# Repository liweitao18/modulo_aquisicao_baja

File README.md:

# modulo_aquisicao_baja
Projeto de modulo de aquisição de dados de um veículo baja SAE

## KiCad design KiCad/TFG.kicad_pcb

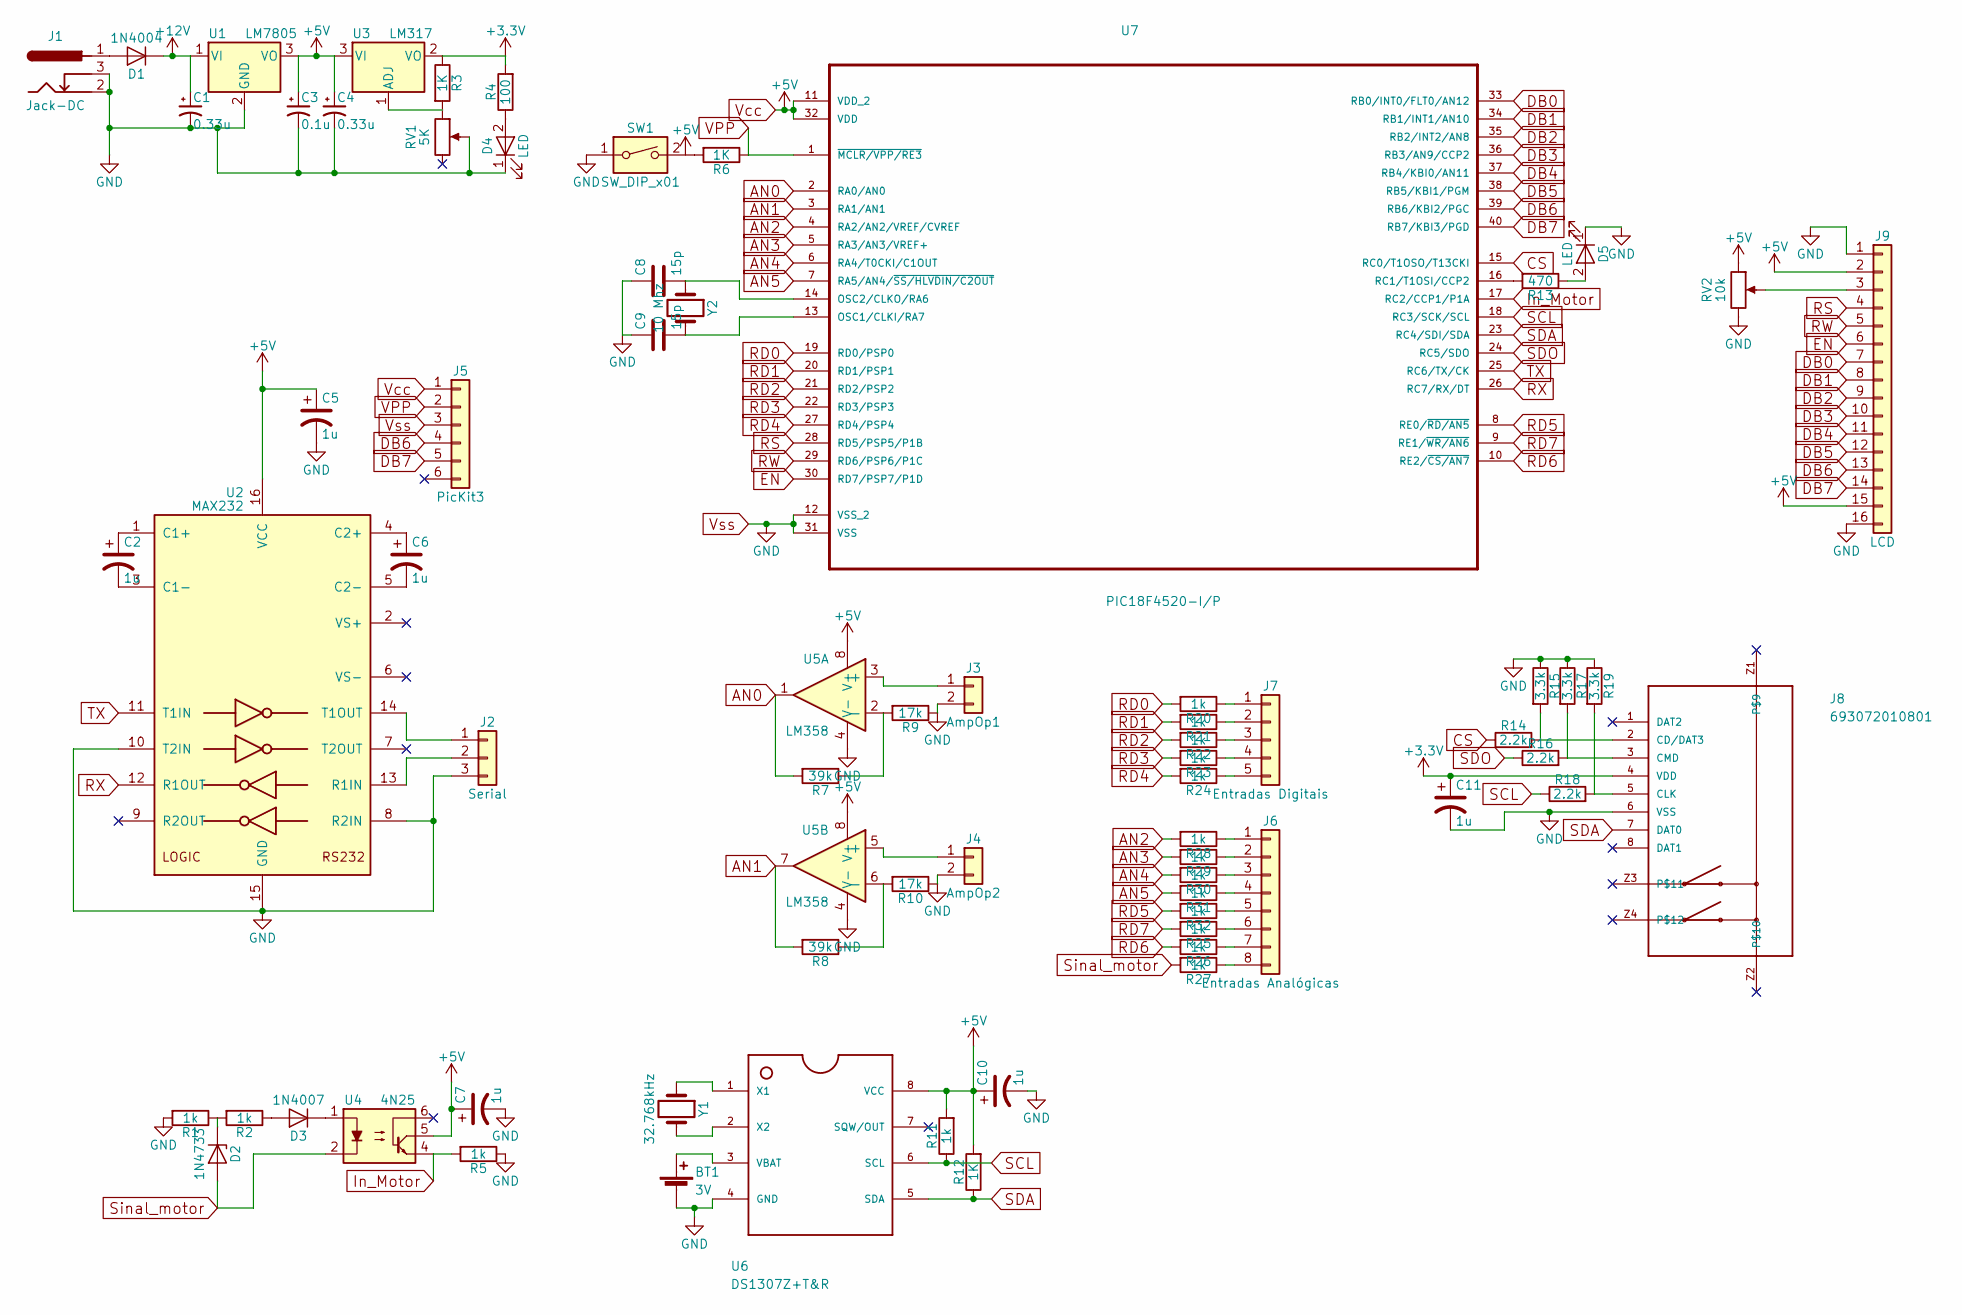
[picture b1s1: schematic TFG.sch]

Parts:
BT1: 3V; Keystone_104_1x23mm-CoinCell
C1, C4: 0.33u; CP_Tantalum_Case-A_EIA-3216-18_Hand
C2, C5, C6, C7, C10, C11: 1u; CP_Tantalum_Case-A_EIA-3216-18_Hand
C3: 0.1u; CP_Tantalum_Case-A_EIA-3216-18_Hand
C8, C9: 15p; C_0201
D1: 1N4004; D_0603
D2: 1N4733; D_0603
D3: 1N4007; D_0603
D4, D5: LED; LED_0402
J1: Jack-DC; GCT_DCJ235-05-A-XX-X_REVA
J2: Serial; Pin_Header_Straight_1x03_Pitch2.00mm
J3: AmpOp1; Pin_Header_Straight_1x02_Pitch2.54mm
J4: AmpOp2; Pin_Header_Straight_1x02_Pitch2.54mm
J5: PicKit3; Pin_Header_Straight_1x06_Pitch2.00mm
J6: Entradas Analógicas; Pin_Header_Straight_1x08_Pitch2.00mm
J7: Entradas Digitais; Pin_Header_Straight_1x05_Pitch2.00mm
J8: 693072010801
J9: LCD; Socket_Strip_Straight_1x16_Pitch2.00mm
R1, R2, R5, R11, R20, R21, R22, R23, R24, R25, R26, R27, R28, R29, R30, R31, R32: 1k; R_0805_HandSoldering
R3, R6, R12: 1K; R_0805_HandSoldering
R4: 100; R_0805_HandSoldering
R7, R8: 39k; R_0805_HandSoldering
R9, R10: 17k; R_0805_HandSoldering
R13: 470; R_0805_HandSoldering
R14, R16, R18: 2.2k; R_0805_HandSoldering
R15, R17, R19: 3.3k; R_0805_HandSoldering
RV1: 5K; Potentiometer_Trimmer_Bourns_3266Y
RV2: 10k; Potentiometer_Trimmer_Bourns_3266Y
SW1: SW_DIP_x01; SW_DIP_x1_W5.08mm_Slide_Copal_CHS-A
U1: LM7805; TO-220-3_Vertical
U2: MAX232; DIP-16_W7.62mm_Socket
U3: LM317; TO-220-3_Vertical
U4: 4N25; DIP-6_W7.62mm_Socket
U5: LM358; DIP-8_W7.62mm_Socket
U6: DS1307Z+T&R; DIP-8_W7.62mm_Socket
U7: PIC18F4520-I/P; DIP254P1524X533-40
Y1: 32.768kHz; Crystal_AT310_d3.0mm_l10.0mm_Vertical
Y2: 10 Mhz; Crystal_HC18-U_Vertical

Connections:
+3V3: C11.1, J8.4 (VDD), R3.1, R4.2, U3.2 (VO)
+12V: C1.1, D1.1 (K), U1.1 (VI)
AN0: R7.2, U5.1, U7.2 (RA0/AN0)
AN1: R8.2, U5.7, U7.3 (RA1/AN1)
AN2: R28.2, U7.4 (RA2/AN2/VREF/CVREF)
AN3: R29.2, U7.5 (RA3/AN3/VREF+)
AN4: R30.2, U7.6 (RA4/T0CKI/C1OUT)
AN5: R31.2, U7.7 (RA5/AN4/~SS/HLVDIN/C2OUT)
CS: R14.1, U7.15 (RC0/T1OSO/T13CKI)
DB0: J9.7, U7.33 (RB0/INT0/FLT0/AN12)
DB1: J9.8, U7.34 (RB1/INT1/AN10)
DB2: J9.9, U7.35 (RB2/INT2/AN8)
DB3: J9.10, U7.36 (RB3/AN9/CCP2)
DB4: J9.11, U7.37 (RB4/KBI0/AN11)
DB5: J9.12, U7.38 (RB5/KBI1/PGM)
DB6: J5.4, J9.13, U7.39 (RB6/KBI2/PGC)
DB7: J5.5, J9.14, U7.40 (RB7/KBI3/PGD)
EN: J9.6, U7.30 (RD7/PSP7/P1D)
In_Motor: R5.2, U4.4, U7.17 (RC2/CCP1/P1A)
unnamed: BT1.1 (+), U6.3 (VBAT)
unnamed: C2.1, U2.1 (C1+)
unnamed: C2.2, U2.3 (C1-)
unnamed: C6.1, U2.4 (C2+)
unnamed: C6.2, U2.5 (C2-)
unnamed: C8.2, U7.14 (OSC2/CLKO/RA6), Y2.1
unnamed: C9.2, U7.13 (OSC1/CLKI/RA7), Y2.2
unnamed: D1.2 (A), J1.1
unnamed: D2.1 (K), R1.1, R2.2
unnamed: D3.1 (K), U4.1
unnamed: D3.2 (A), R2.1
unnamed: D4.2 (A), R4.1
unnamed: D5.2 (A), R13.1
unnamed: J2.1, U2.14 (T1OUT)
unnamed: J2.2, U2.13 (R1IN)
unnamed: J3.1, U5.3 (+)
unnamed: J4.1, U5.5 (+)
unnamed: J6.1, R28.1
unnamed: J6.2, R29.1
unnamed: J6.3, R30.1
unnamed: J6.4, R31.1
unnamed: J6.5, R32.1
unnamed: J6.6, R25.1
unnamed: J6.7, R26.1
unnamed: J6.8, R27.1
unnamed: J7.1, R20.1
unnamed: J7.2, R21.1
unnamed: J7.3, R22.1
unnamed: J7.4, R23.1
unnamed: J7.5, R24.1
unnamed: J8.2 (CD/DAT3), R14.2, R15.2
unnamed: J8.3 (CMD), R16.2, R17.2
unnamed: J8.5 (CLK), R18.2, R19.2
unnamed: J9.3, RV2.2
unnamed: R3.2, RV1.1, U3.1 (ADJ)
unnamed: R6.2, SW1.2
unnamed: R7.1, R9.2, U5.2 (-)
unnamed: R8.1, R10.2, U5.6 (-)
unnamed: R13.2, U7.16 (RC1/T1OSI/CCP2)
unnamed: U6.1 (X1), Y1.1
unnamed: U6.2 (X2), Y1.2
RD0: R20.2, U7.19 (RD0/PSP0)
RD1: R21.2, U7.20 (RD1/PSP1)
RD2: R22.2, U7.21 (RD2/PSP2)
RD3: R23.2, U7.22 (RD3/PSP3)
RD4: R24.2, U7.27 (RD4/PSP4)
RD5: R32.2, U7.8 (RE0/~RD/AN5)
RD6: R26.2, U7.10 (RE2/~CS/AN7)
RD7: R25.2, U7.9 (RE1/~WR/AN6)
RS: J9.4, U7.28 (RD5/PSP5/P1B)
RW: J9.5, U7.29 (RD6/PSP6/P1C)
RX: U2.12 (R1OUT), U7.26 (RC7/RX/DT)
SCL: R11.1, R18.1, U6.6 (SCL), U7.18 (RC3/SCK/SCL)
SDA: J8.7 (DAT0), R12.1, U6.5 (SDA), U7.23 (RC4/SDI/SDA)
SDO: R16.1, U7.24 (RC5/SDO)
Sinal_motor: D2.2 (A), R27.2, U4.2
TX: U2.11 (T1IN), U7.25 (RC6/TX/CK)
VPP: J5.2, R6.1, U7.1 (~MCLR/VPP/RE3)
Vcc: C3.1, C4.1, C5.1, C7.1, C10.1, J5.1, J9.2, J9.15, R11.2, R12.2, RV2.1, U1.3 (VO), U2.16 (VCC), U3.3 (VI), U4.5, U5.8 (V+), U6.8 (VCC), U7.11 (VDD_2), U7.32 (VDD)
Vss: BT1.2 (-), C1.2, C3.2, C4.2, C5.2, C7.2, C8.1, C9.1, C10.2, C11.2, D4.1 (K), D5.1 (K), J1.2, J1.3, J2.3, J3.2, J4.2, J5.3, J8.6 (VSS), J9.1, J9.16, R1.2, R5.1, R9.1, R10.1, R15.1, R17.1, R19.1, RV1.2, RV2.3, SW1.1, U1.2 (GND), U2.8 (R2IN), U2.10 (T2IN), U2.15 (GND), U5.4 (V-), U6.4 (GND), U7.12 (VSS_2), U7.31 (VSS)

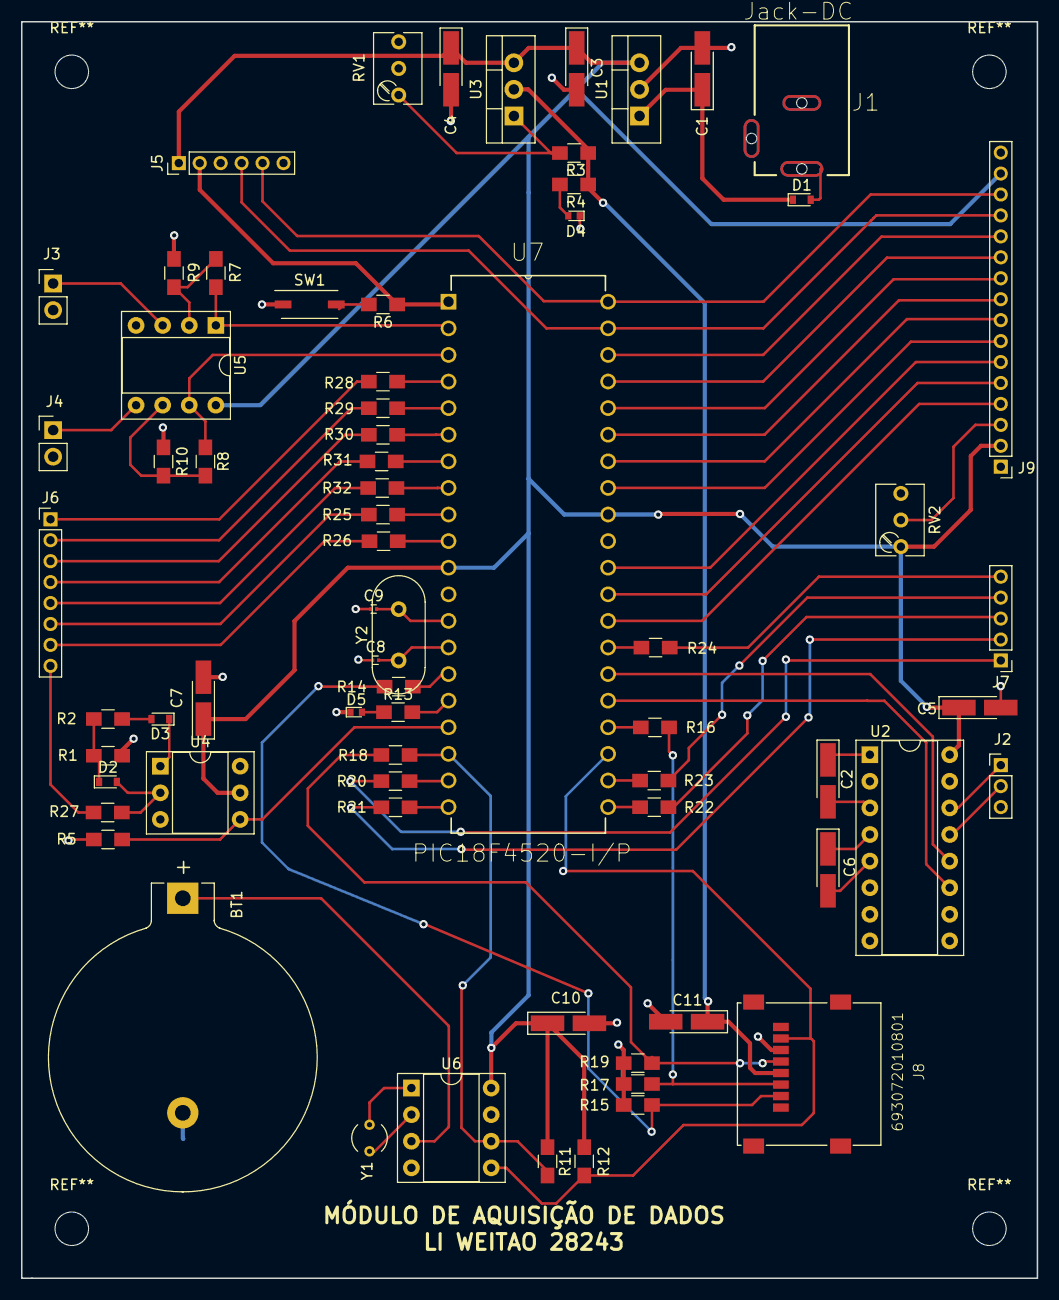
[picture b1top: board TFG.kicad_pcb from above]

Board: 2 copper layers, 97.0 x 120.0 mm, 70 parts (0 on the bottom side), 79 nets.

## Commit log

2018-06-04 Create KiCad
2018-06-04 git add -A
